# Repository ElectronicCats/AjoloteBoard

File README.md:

View this project on [CADLAB.io](https://cadlab.io/project/1720). 

# Ajolote Board Kit

Las insignias de ajolote son insoportablemente lindas. Creadas especialmente para enseñar a cualquier persona a soldar su primer tarjeta electrónica; es un kit de soldadura muy básico y adecuado para todas las edades.

¡Este kit de Ajolote tiene dos LED de colores con patrones de luz diferentes! El interruptor te permite encender o apagar el dispositivo y un holder de batería.

Una vez que el kit de insignia está soldado y la batería insertada, el LED de la insignia parpadea y cambia de color durante aproximadamente 24 horas. Puedes usarlo como un pin en tu ropa, un collar, de llavero o en una pulsera
Se requieren habilidades de soldadura muy básicas.

Por amor a los ajolotes, conciencia de su preservación y orgulloso patrimonio mexicano, nos hemos unido a la Asociación Civil [“Redes y Restauración Ecologica”](http://www.redesmx.org/) , destinando el 50% de las ganancias del kit y sea utilizado para ayuda del ajolote y su hábitad natural, así como la concientización que representa su conservación.

### [Disponible en nuestra tienda](https://electroniccats.com/producto/pre-order-ajolote-board-kit/)

## Licence

Hardware released under an CERN Open Hardware Licence v1.2. See the LICENSE_HARDWARE file for more information.

Electronic Cats is a registered trademark, please do not use if you sell these PCBs.

Electronic Cats invests time and resources providing this open source design, please support Electronic Cats and open-source hardware by purchasing products from Electronic Cats!

Designed by Electronic Cats.

17 April 2018

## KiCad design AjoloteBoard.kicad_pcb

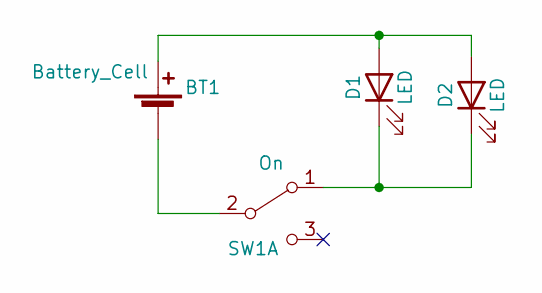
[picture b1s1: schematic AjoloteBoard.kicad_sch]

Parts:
BT1: Battery_Cell; BAT-HLD-001
D1, D2: LED; LED_D5.0mm_Clear
SW1: On; JS102011SAQN

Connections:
unnamed: BT1.2 (+), D1.2 (A), D2.2 (A)
unnamed: BT1.1 (-), SW1.2 (B)
unnamed: D1.1 (K), D2.1 (K), SW1.1 (A)

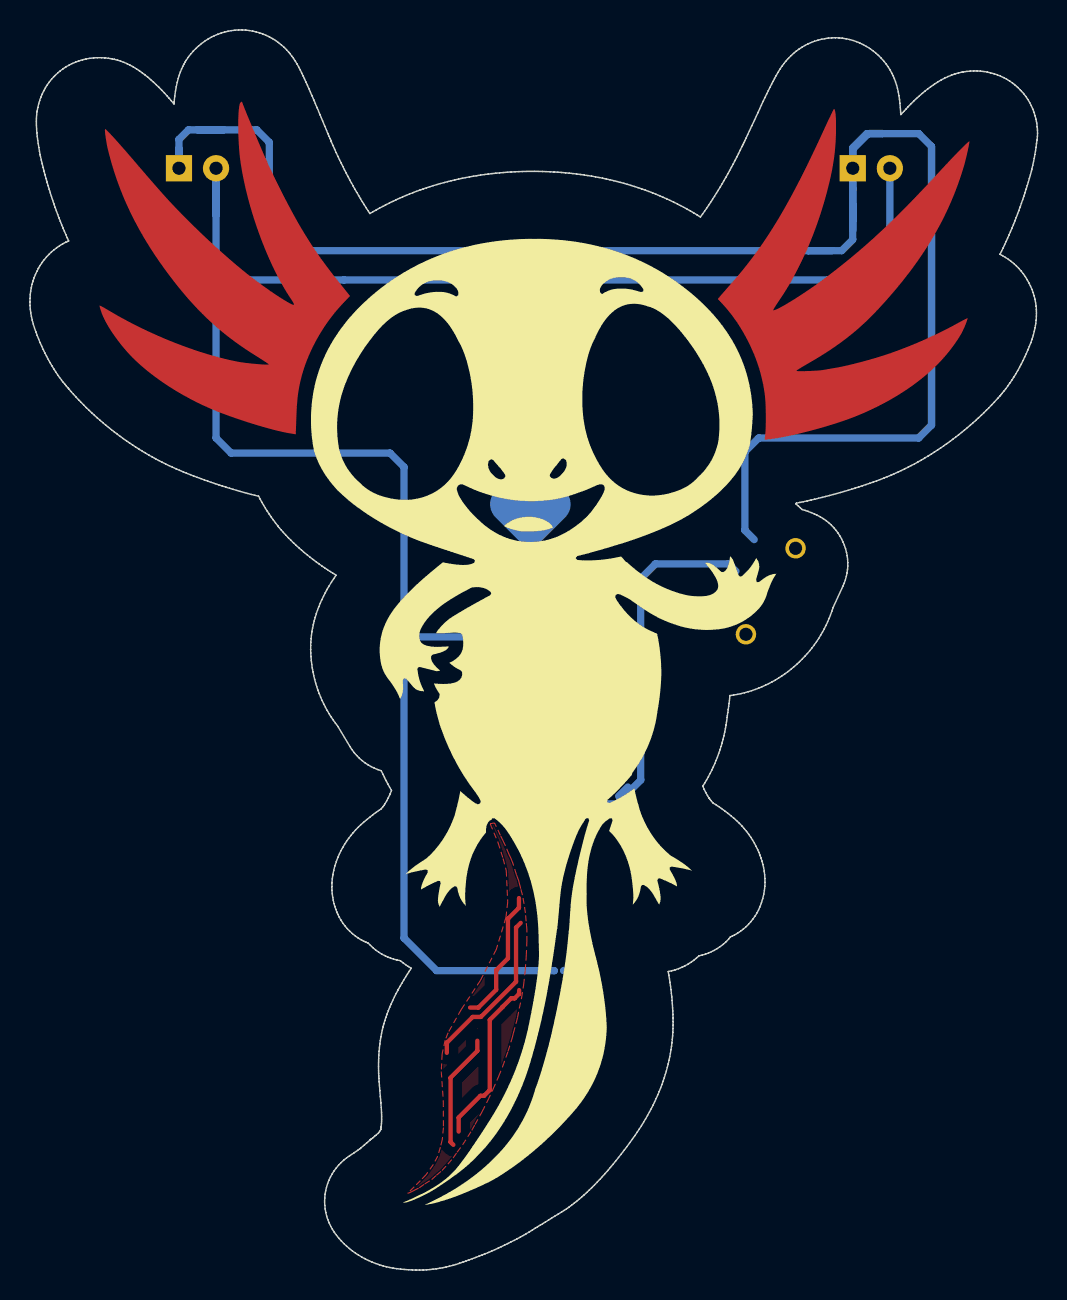
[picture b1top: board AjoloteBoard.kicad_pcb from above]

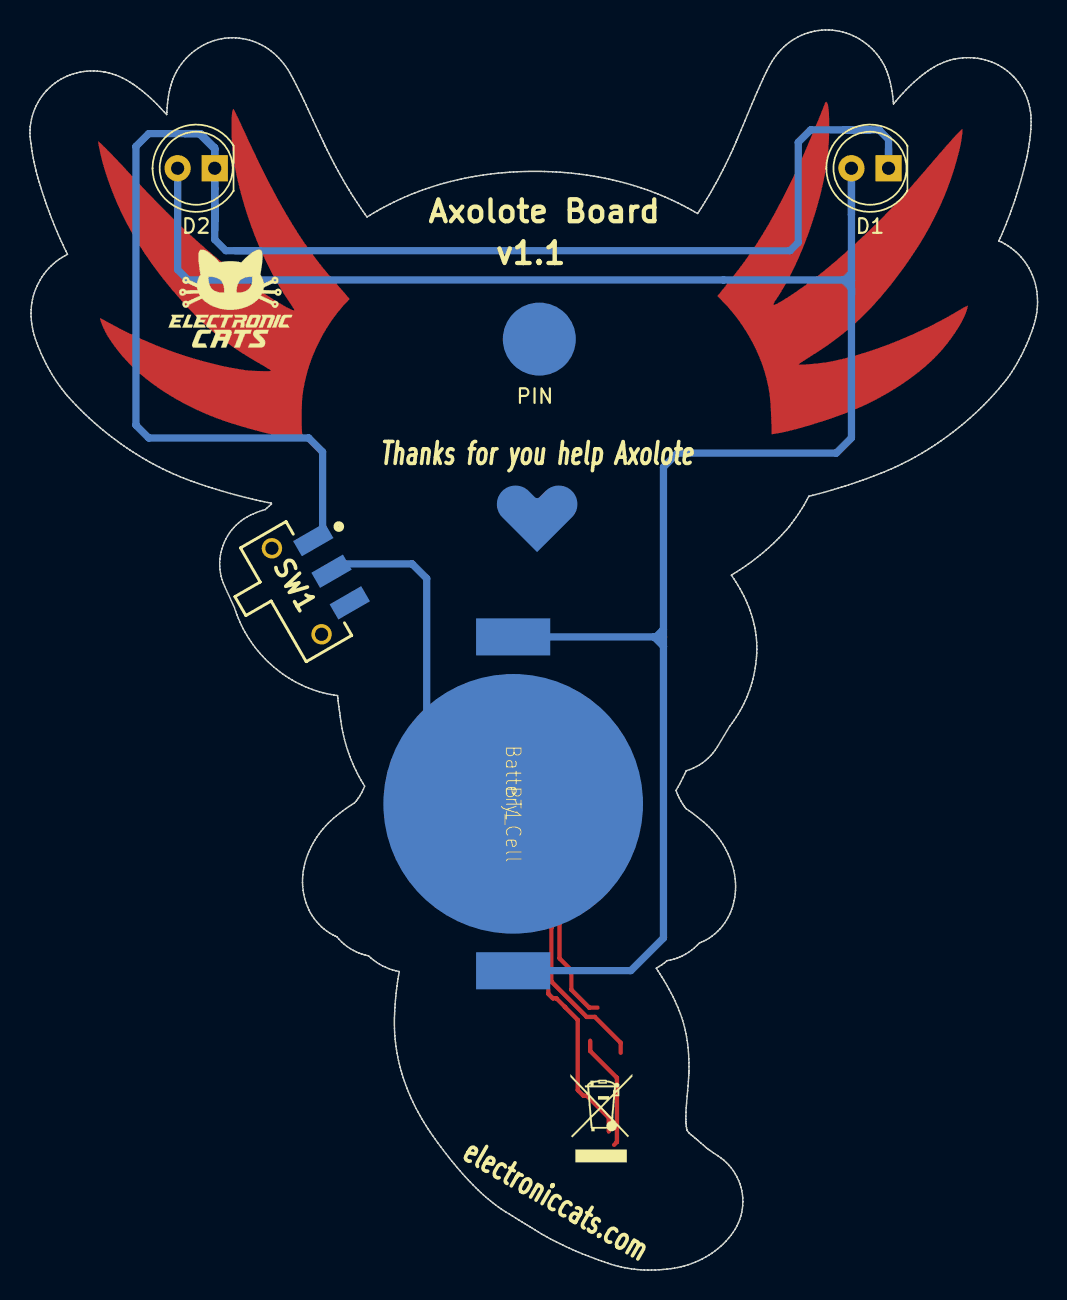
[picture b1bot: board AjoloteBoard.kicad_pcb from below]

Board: 2 copper layers, 69.0 x 84.9 mm, 7 parts (6 on the bottom side), 3 nets.

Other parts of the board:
PIN: Tacks_tachuelas
svg2mod: ajolote; svg2mod
svg2mod#2: G***; heart

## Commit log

2018-06-11 Schematic and PCB
2018-06-11 Update README in spanish
2018-06-11 Fix link
2018-06-23 SilkS for leds
2018-11-28 fix tracks
2018-11-28 Update kicad version
2019-04-28 Backlink to CADLAB.io has been added.
2019-05-08 fix inverted leds
2019-10-15 add assets and footprints extras
2019-10-15 update footprints folder
2019-10-15 Update project to kicad 5
2019-10-15 Update foorprints and floor plan
2019-10-15 update micro interruptor pinout
2019-10-15 Add logos wurth
2019-10-15 add heart logo
2019-10-15 add 3d files
2019-10-15 add wurth switch
2019-10-17 Add logo de PCBWay
2020-02-13 silks led to back
2020-08-25 Create LICENSE_HARDWARE
2020-08-27 OpenSourceLicense
2023-06-01 Battery holder and switch changed
2023-06-15 Corrected battery routing
